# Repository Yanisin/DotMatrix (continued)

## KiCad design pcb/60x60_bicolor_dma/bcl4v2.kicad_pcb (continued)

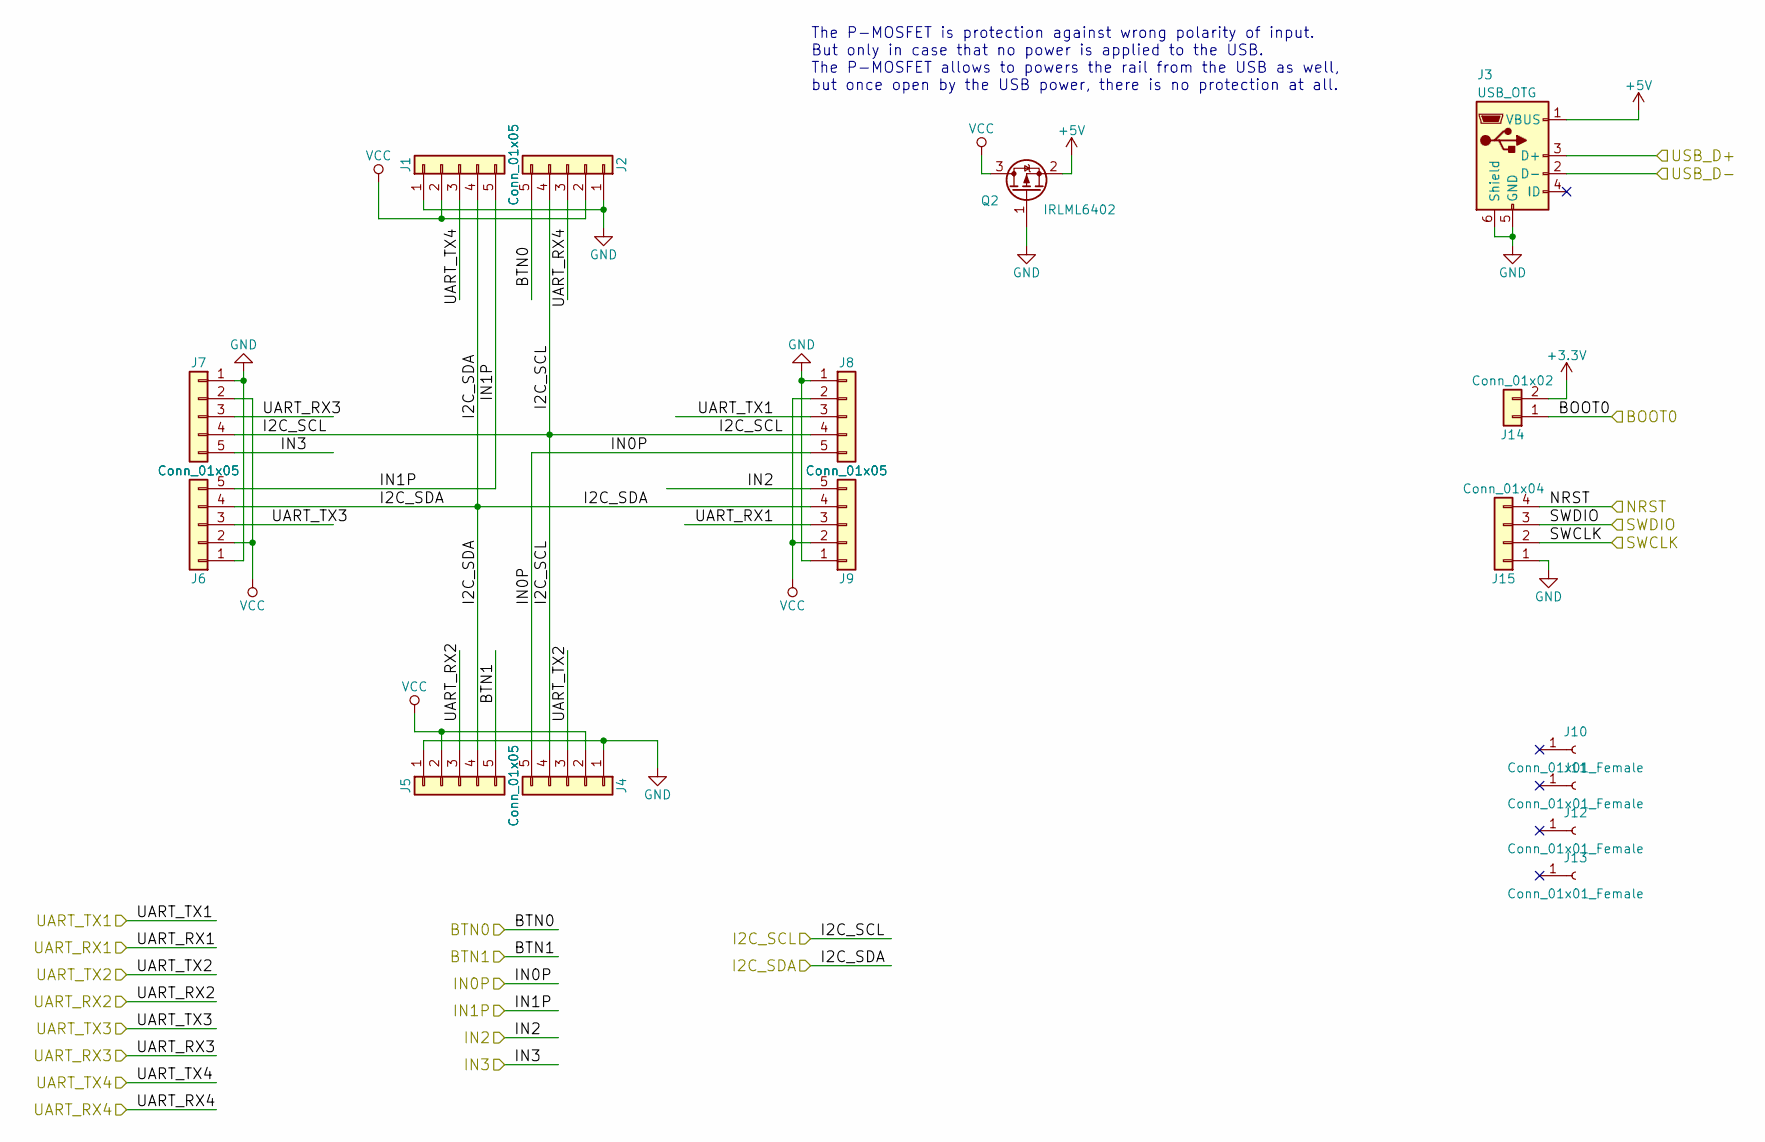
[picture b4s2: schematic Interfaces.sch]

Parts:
J1, J2, J4, J5, J6, J7, J8, J9: Conn_01x05; badger_Pin_Hdr_1x05_2.54mm_handsolder
J3: USB_OTG; USB_Micro-B
J10, J11, J12, J13: Conn_01x01_Female; badger_mount_M3
J14: Conn_01x02; badger_Pin_Hdr_1x02_2.54mm_angled_handsolder
J15: Conn_01x04; badger_Pin_Hdr_1x04_2.54mm_angled_handsolder
Q2: IRLML6402; badger_SOT-23_handsolder

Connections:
+3V3: J14.2; also elsewhere on the board
+5V: J3.1 (VBUS), Q2.2 (S); also elsewhere on the board
/BOOT0: J14.1; also elsewhere on the board
/BTN0: J2.5; also elsewhere on the board
/BTN1: J5.5; also elsewhere on the board
/I2C_SCL: J2.4, J4.4, J7.4, J8.4; also elsewhere on the board
/I2C_SDA: J1.4, J5.4, J6.4, J9.4; also elsewhere on the board
/IN0P: J4.5, J8.5; also elsewhere on the board
/IN1P: J1.5, J6.5; also elsewhere on the board
/IN2: J9.5; also elsewhere on the board
/IN3: J7.5; also elsewhere on the board
/NRST: J15.4; also elsewhere on the board
/SWCLK: J15.2; also elsewhere on the board
/SWDIO: J15.3; also elsewhere on the board
/UART_RX1: J9.3; also elsewhere on the board
/UART_RX2: J5.3; also elsewhere on the board
/UART_RX3: J7.3; also elsewhere on the board
/UART_RX4: J2.3; also elsewhere on the board
/UART_TX1: J8.3; also elsewhere on the board
/UART_TX2: J4.3; also elsewhere on the board
/UART_TX3: J6.3; also elsewhere on the board
/UART_TX4: J1.3; also elsewhere on the board
/USB_D+: J3.3 (D+); also elsewhere on the board
/USB_D-: J3.2 (D-); also elsewhere on the board
GND: J1.1, J2.1, J3.5 (GND), J3.6 (Shield), J4.1, J5.1, J6.1, J7.1, J8.1, J9.1, J15.1, Q2.1 (G); also elsewhere on the board
VCC: J1.2, J2.2, J4.2, J5.2, J6.2, J7.2, J8.2, J9.2, Q2.3 (D)

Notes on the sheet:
The P-MOSFET is protection against wrong polarity of input. But only in case that no power is applied to the USB. The P-MOSFET allows to powers the rail from the USB as well, but once open by the USB power, there is no protection at all.

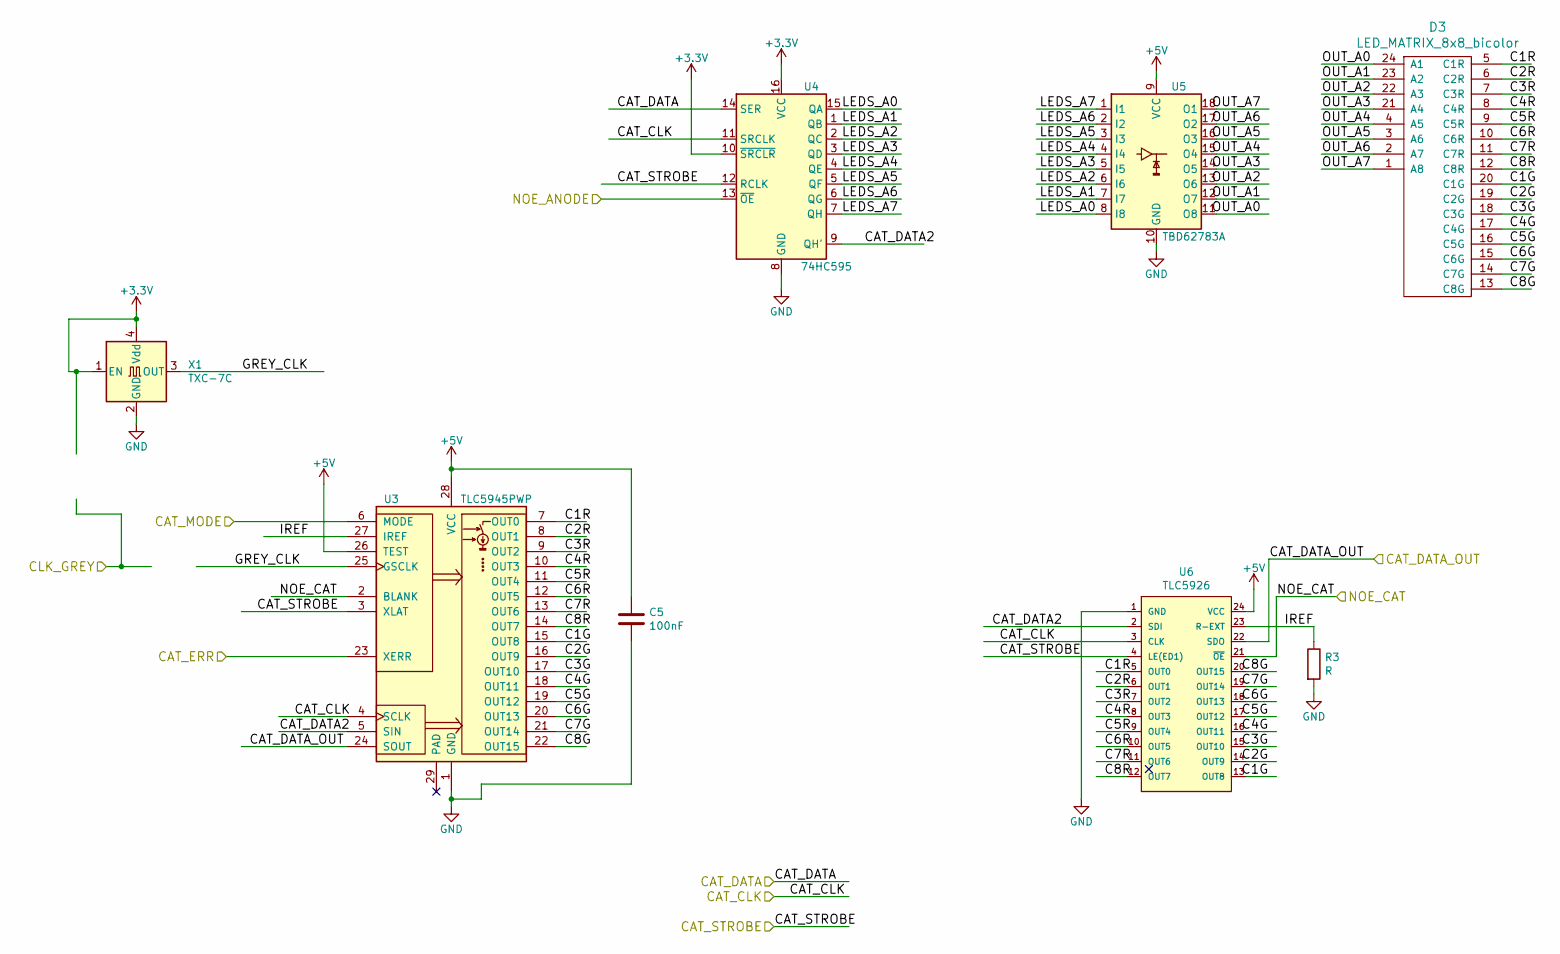
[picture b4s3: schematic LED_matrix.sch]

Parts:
C5: 100nF; C_0805_HandSoldering
D3: LED_MATRIX_8x8_bicolor; badger_LED_MATRIX_8x8_60.2mmx60.2mm_bicolor
R3: R; R_0805_HandSoldering
U3: TLC5945PWP; HTSSOP-28_4.4x9.7mm_Pitch0.65mm_wo_thermal_pad
U4: 74HC595; SO-16-N
U5: TBD62783A; SOIC-18W_7.5x11.6mm_Pitch1.27mm
U6: TLC5926; SOIC-24W_7.5x15.4mm_Pitch1.27mm
X1: TXC-7C; Oscillator_SMD_EuroQuartz_XO53-4pin_5.0x3.2mm_HandSoldering

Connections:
+3V3: U4.10 (~SRCLR), U4.16 (VCC), X1.1 (EN), X1.4 (Vdd); also elsewhere on the board
+5V: C5.1, U3.26 (TEST), U3.28 (VCC), U5.9 (VCC), U6.24 (VCC); also elsewhere on the board
/CAT_CLK: U3.4 (SCLK), U4.11 (SRCLK), U6.3 (CLK); also elsewhere on the board
/CAT_DATA: U4.14 (SER); also elsewhere on the board
/CAT_DOUT: U3.24 (SOUT), U6.22 (SDO); also elsewhere on the board
/CAT_ERR: U3.23 (XERR); also elsewhere on the board
/CAT_MODE: U3.6 (MODE); also elsewhere on the board
/CAT_STROBE: U3.3 (XLAT), U4.12 (RCLK), U6.4 (LE(ED1)); also elsewhere on the board
/LED_matrix/C1G: D3.20 (C1G), U3.15 (OUT8), U6.13 (OUT8)
/LED_matrix/C1R: D3.5 (C1R), U3.7 (OUT0), U6.5 (OUT0)
/LED_matrix/C2G: D3.19 (C2G), U3.16 (OUT9), U6.14 (OUT9)
/LED_matrix/C2R: D3.6 (C2R), U3.8 (OUT1), U6.6 (OUT1)
/LED_matrix/C3G: D3.18 (C3G), U3.17 (OUT10), U6.15 (OUT10)
/LED_matrix/C3R: D3.7 (C3R), U3.9 (OUT2), U6.7 (OUT2)
/LED_matrix/C4G: D3.17 (C4G), U3.18 (OUT11), U6.16 (OUT11)
/LED_matrix/C4R: D3.8 (C4R), U3.10 (OUT3), U6.8 (OUT3)
/LED_matrix/C5G: D3.16 (C5G), U3.19 (OUT12), U6.17 (OUT12)
/LED_matrix/C5R: D3.9 (C5R), U3.11 (OUT4), U6.9 (OUT4)
/LED_matrix/C6G: D3.15 (C6G), U3.20 (OUT13), U6.18 (OUT13)
/LED_matrix/C6R: D3.10 (C6R), U3.12 (OUT5), U6.10 (OUT5)
/LED_matrix/C7G: D3.14 (C7G), U3.21 (OUT14), U6.19 (OUT14)
/LED_matrix/C7R: D3.11 (C7R), U3.13 (OUT6), U6.11 (OUT6)
/LED_matrix/C8G: D3.13 (C8G), U3.22 (OUT15), U6.20 (OUT15)
/LED_matrix/C8R: D3.12 (C8R), U3.14 (OUT7), U6.12 (OUT7)
/LED_matrix/CAT_DATA2: U3.5 (SIN), U4.9 (QH'), U6.2 (SDI)
/LED_matrix/GREY_CLK: U3.25 (GSCLK), X1.3 (OUT)
/LED_matrix/IREF: R3.1, U3.27 (IREF), U6.23 (R-EXT)
/LED_matrix/LEDS_A0: U4.15 (QA), U5.8 (I8)
/LED_matrix/LEDS_A1: U4.1 (QB), U5.7 (I7)
/LED_matrix/LEDS_A2: U4.2 (QC), U5.6 (I6)
/LED_matrix/LEDS_A3: U4.3 (QD), U5.5 (I5)
/LED_matrix/LEDS_A4: U4.4 (QE), U5.4 (I4)
/LED_matrix/LEDS_A5: U4.5 (QF), U5.3 (I3)
/LED_matrix/LEDS_A6: U4.6 (QG), U5.2 (I2)
/LED_matrix/LEDS_A7: U4.7 (QH), U5.1 (I1)
/LED_matrix/OUT_A0: D3.24 (A1), U5.11 (O8)
/LED_matrix/OUT_A1: D3.23 (A2), U5.12 (O7)
/LED_matrix/OUT_A2: D3.22 (A3), U5.13 (O6)
/LED_matrix/OUT_A3: D3.21 (A4), U5.14 (O5)
/LED_matrix/OUT_A4: D3.4 (A5), U5.15 (O4)
/LED_matrix/OUT_A5: D3.3 (A6), U5.16 (O3)
/LED_matrix/OUT_A6: D3.2 (A7), U5.17 (O2)
/LED_matrix/OUT_A7: D3.1 (A8), U5.18 (O1)
/NOE_ANODE: U4.13 (~OE); also elsewhere on the board
/NOE_CAT: U3.2 (BLANK), U6.21 (~OE); also elsewhere on the board
GND: C5.2, R3.2, U3.1 (GND), U4.8 (GND), U5.10 (GND), U6.1 (GND), X1.2 (GND); also elsewhere on the board

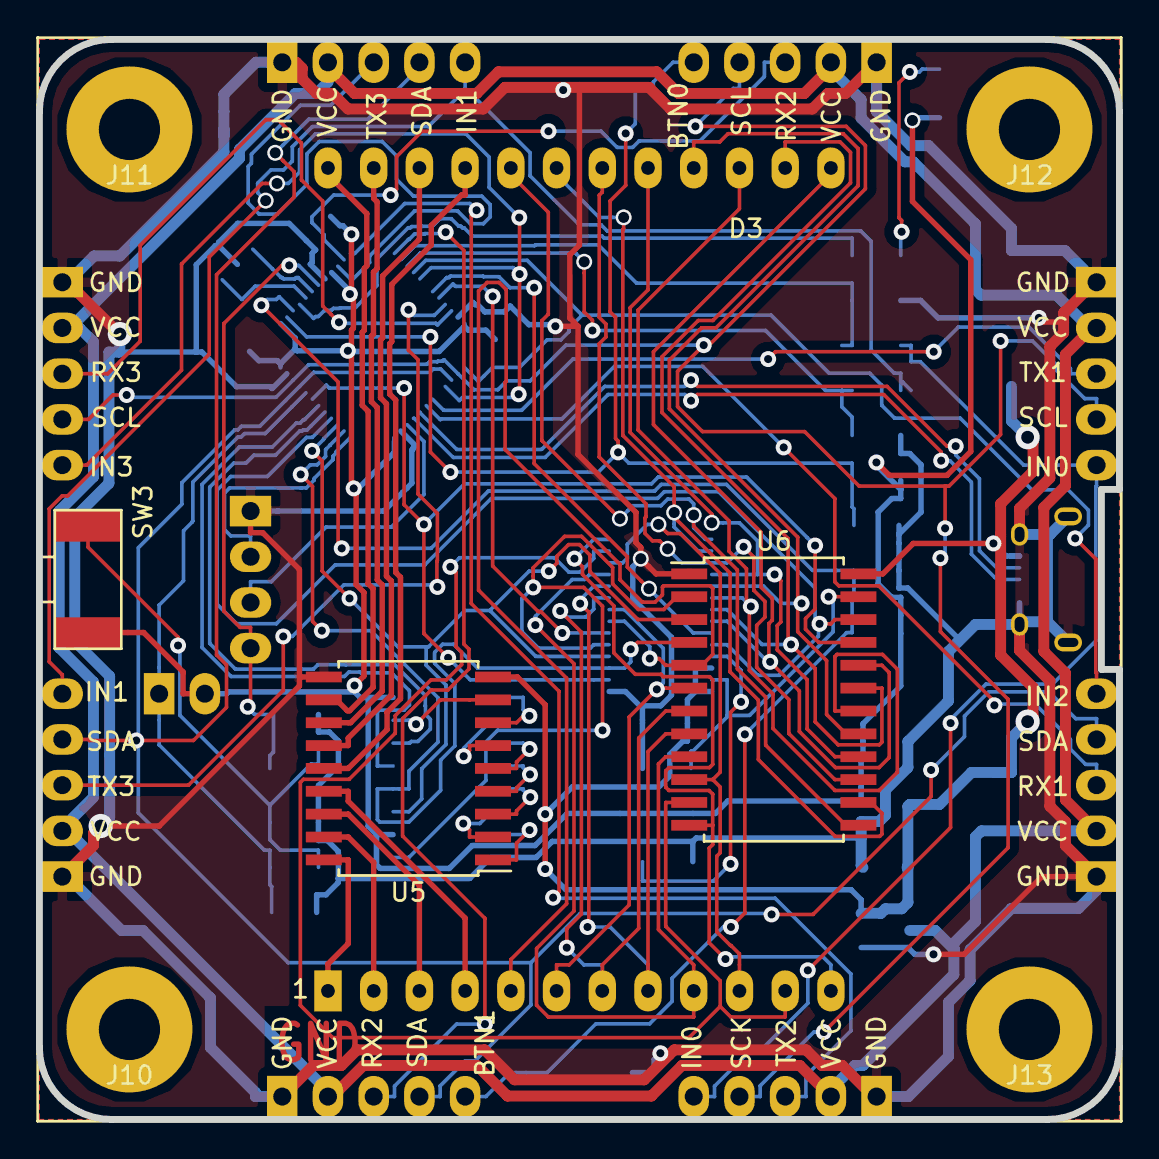
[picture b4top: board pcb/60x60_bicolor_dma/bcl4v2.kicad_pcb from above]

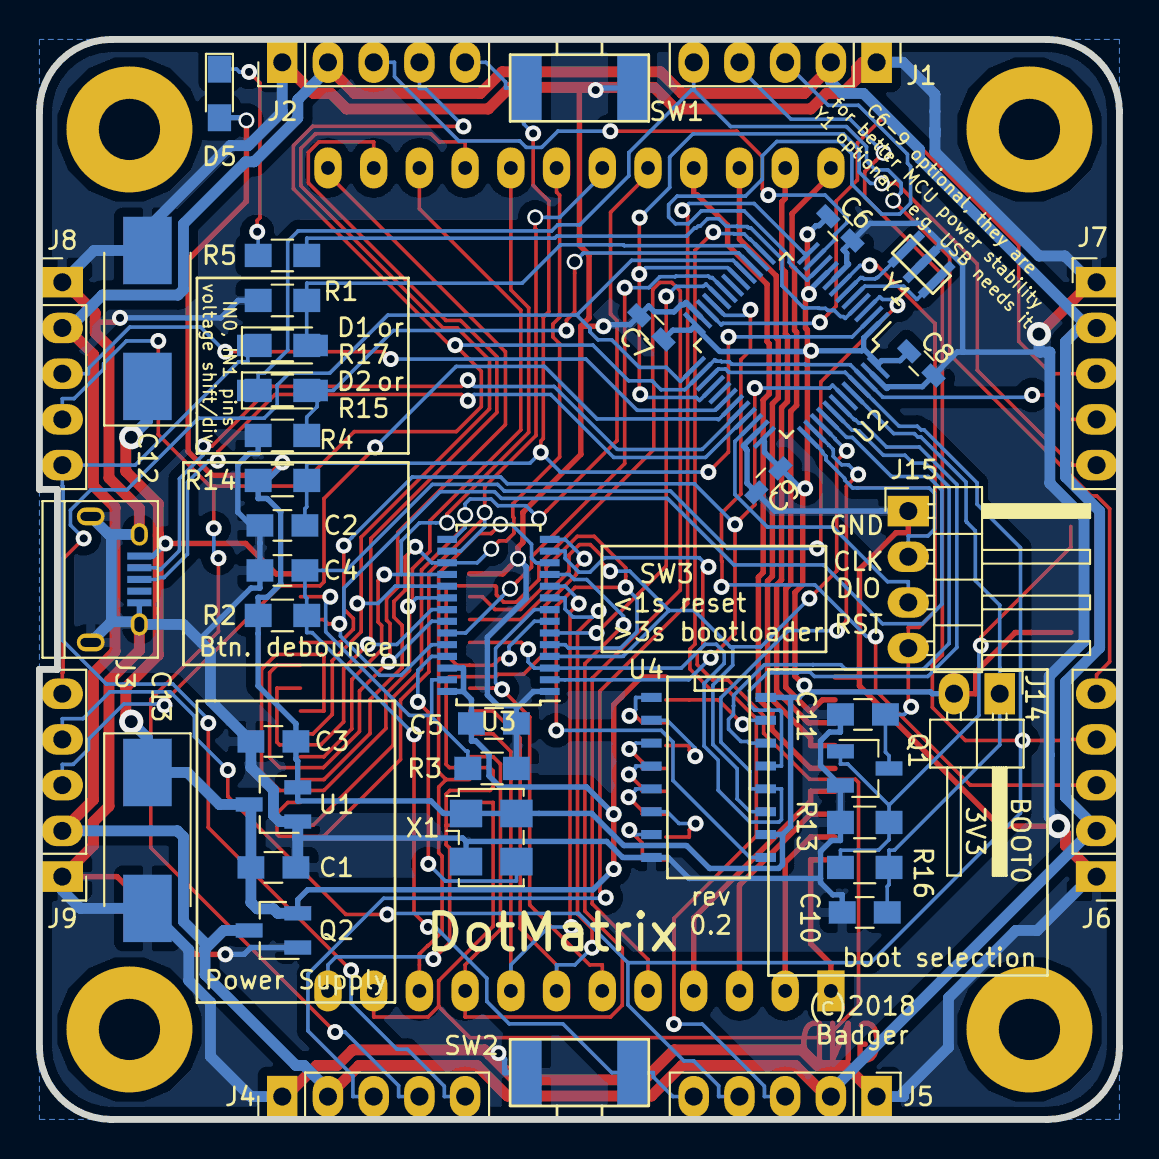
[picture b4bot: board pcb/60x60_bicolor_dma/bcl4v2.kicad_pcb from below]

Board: 2 copper layers, 60.0 x 60.0 mm, 55 parts (47 on the bottom side), 76 nets.

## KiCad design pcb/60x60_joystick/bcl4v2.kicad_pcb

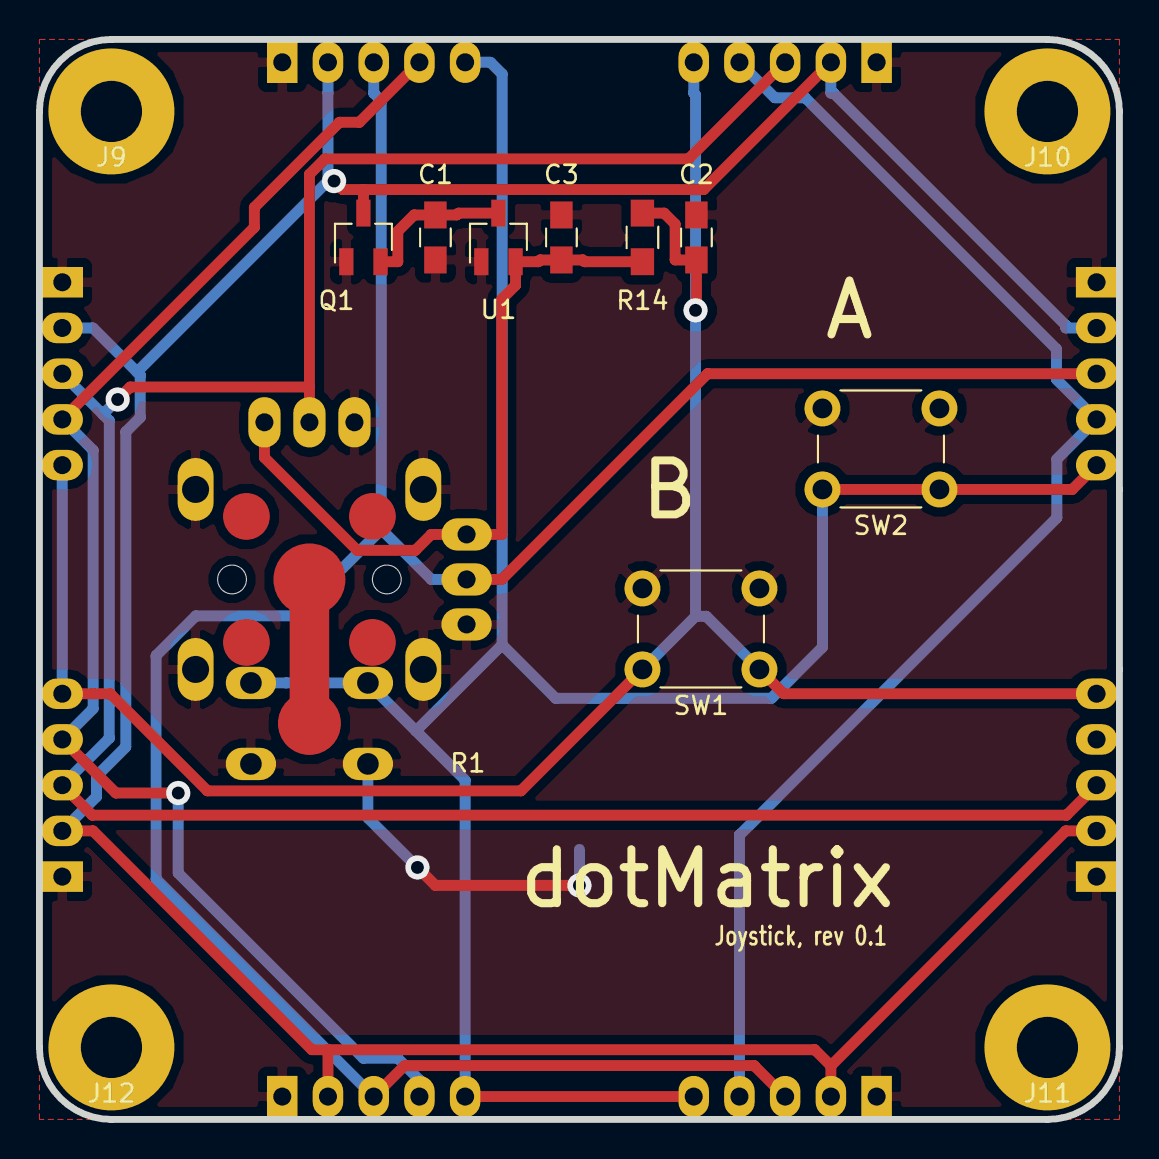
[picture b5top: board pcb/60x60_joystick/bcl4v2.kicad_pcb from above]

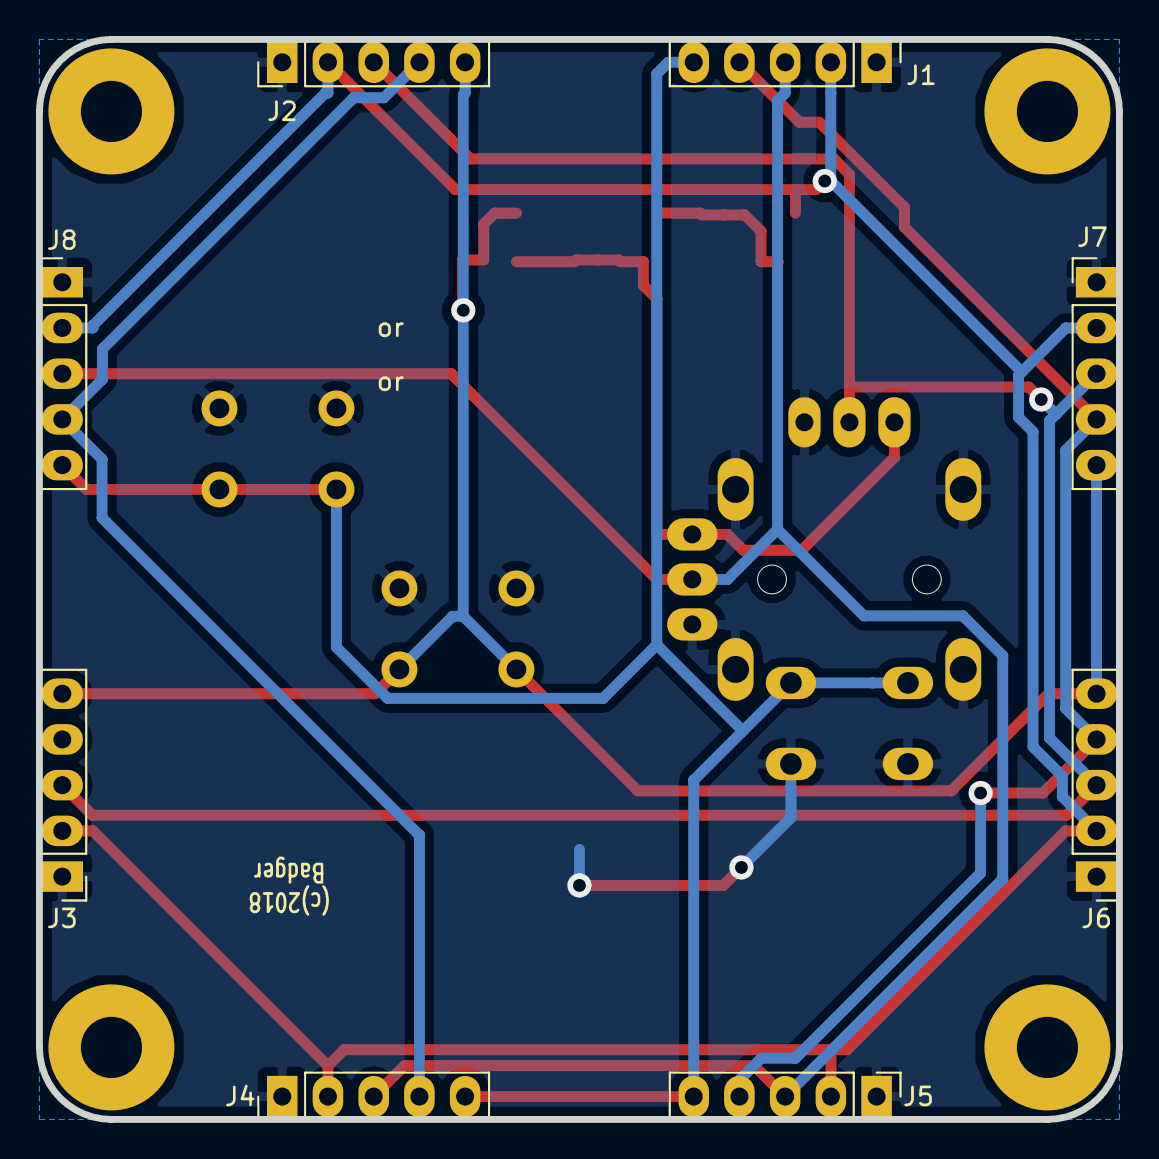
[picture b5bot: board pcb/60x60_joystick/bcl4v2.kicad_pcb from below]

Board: 2 copper layers, 60.0 x 60.0 mm, 21 parts (8 on the bottom side), 10 nets.

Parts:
C1, C3: 4u7; C_0805_HandSoldering
C2: 100n; C_0805_HandSoldering
J1, J2, J3, J4, J5, J6, J7, J8: Conn_01x05; badger_Pin_Hdr_1x05_2.54mm_handsolder
J9, J10, J11, J12: Conn_01x01_Female; badger_mount_M3
Q1: IRLML6402; badger_SOT-23_handsolder
R1: RKJXV1224_Joystick; badger_RKJXV1224 Joystick
R14: 220k; R_0805_HandSoldering
SW1, SW2: SW_Push; SW_PUSH_6mm_h5mm
U1: DS9166A-23; badger_SOT-23_handsolder

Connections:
+3V3: C3.1, R1.1, R1.4, R14.1, U1.2
+5V: C1.1, Q1.2, U1.3
/AOUT0: J2.3, J3.3, J6.3, J7.3, R1.2
/AOUT1: J1.3, J4.3, J5.3, J8.3, R1.5
/BTN0: J1.5, J4.5, J5.5, J8.5, R1.7, R1.8, SW2.1
/BTN1: C2.2, J2.5, J3.5, J6.5, J7.5, R14.2, SW1.1
/I2C_SCL: J1.4, J5.4, J6.4, J7.4
/I2C_SDA: J2.4, J4.4, J8.4
GND: C1.2, C2.1, C3.2, J1.1, J2.1, J3.1, J4.1, J5.1, J6.1, J7.1, J8.1, Q1.1, R1.3, R1.6, R1.9, R1.10, R1.11, R1.12, R1.13, R1.14, SW1.2, SW2.2, U1.1
VCC: J1.2, J2.2, J3.2, J4.2, J5.2, J6.2, J7.2, J8.2, Q1.3

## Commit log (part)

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2018-10-25 - add first prototype version of PCB
2018-10-25 - add some demos sketches without much of cleaning
2018-10-25 - use the CERN OHL v1.2
2018-10-28 - add errata for HW revision 0.1
2018-10-28 - draft of 60x60mm version
2018-10-28 - brainstorming what can be connected to headers
2018-10-28 - make the headers better solderable
2018-10-29 - split schematics to more pages
2018-11-01 - add pins to the sheets, add reset/boot circuit
2018-11-03 - replaced protection LEDs with mosfet
2018-11-03 - pcb (hopefully) ready for first routing attempt
2018-11-03 - little bit more componnent shifting to ease soldering
2018-11-03 -add missing LCD component footprint
2018-11-03 - don't commit kicad backup files
2018-11-03 - fix some footprints to reduce ERC errors
2018-11-03 - no need for edge cut for USB here
2018-11-03 - just before importing routed pcb from freeroute
2018-11-03 - imported freeroute output
2018-11-03 - fix silkscreen
2018-11-03 - yet another silkscreen fine tuning
2018-11-12 - add note about mounting hole spacing
2018-11-13 Add LED matrix symbol/footprint
2018-11-13 Board update
    fully routed PCB
    indicator LED added
2018-11-14 Add STEP model for USB receptacle
    Source:
    https://www.digikey.com/product-detail/en/amphenol-fci/10118194-0001LF/609-4618-1-ND/2785382
2018-11-18 PCB updates for panelization
    - place USB receptacle and edge cut-out smack center of the right board edge
    - rounded cut-out (.4mm radius) to allow routing it out using a single
    0.8mm wide slot.
2018-11-19 - quick sketch of bicolor 60x60 pcb
2018-11-25 - add prg_usb target
2018-11-25 - don't commit results of build process
2018-11-25 - add missing header, more cleanup
2018-11-25 - don't commit bin files
2018-11-25 - make hw config selectable during compile time
2018-11-25 - switch to next hw revision
2018-11-27 PCB and schematics cleanup
    resize PCB to exactly 38x38mm, center the LED matrix
    add OSHW logo to silk screen, add copyright information
2018-11-28 prg: use the "program" macro to flash the target
    canonical method to flash a target is:
    "program ELF.elf verify reset exit"
    which takes care of everything. ELF file must be linked for the correct
    address in flash.
2018-11-28 Makefile: provide TOPDIR variable
    useful to address OPENCM3 relative to the project root.
2018-11-30 Add test points, small routing changes
    - add test points for SPI bus
    - add net classes for VCC and LED networks
    - small routing changes
2018-12-05 correct dependency for "prg" target
    oocd programming only needs the ELF file
    also, use the preset OOCD variable to start openocd
2018-12-07 Support for 38x38 v3 tile with DMA
    Lots of changes in this one
    - display scan-out with DMA
    - remove generic timer interrupts
    - PRNG with xorshift32
    - overall clean-up, removing lots of dead and ifdef'd code,
    formatting cleanup
2018-12-07 make life less boring
    - fix rule computation, cell death must be instant, but life may have
    shades of red
    - add a few heuristics to catch stagnant (boring) populations
2018-12-07 small pcb fixes
    move USB_VBUS via out from under the USB receptacle (ouch)
    it just makes handsoldering difficult because the shield of
    the receptacle sucks up superfluous tin and then shorts
    USB_VBUS to ground
2018-12-14 disp: add fast version of disp_set
    add disp_set_noupdate() which only sets the display buffer
    but doesn't update the DMA row buffer. Useful for bulk
    updates of the display that touch all rows multiple times.
    also add disp_update_rows() to update all DMA row buffers
    at once.
2018-12-14 usart: new method for USART assignment to edge
    USARTS are now internally enumerated from A to D and their
    base pointers are stored in an array indexed from 0 to 3.
    Assignment of edges to USARTS is through symbolic name
    USART_[A-D]. usart_init() needs to be called in order
    A to D to match ISR assignments of rx/tx buffers.
    Also some cleanups and removal of dead/commented code.
2018-12-21 Correct display orientation to make (0,0) top left
    hardware should be reflected in the software.
2018-12-21 refactor usart_buffered.c
    - move common isr code into single function
    - simplify ring buffer operations, make them easier to understand
2019-01-01 Add CDCACM USB function
    Serial line for debug and control
2019-01-01 Cleanup main()
    add cpu_relax() inline function to execute "wfi" in the main loop
    general cleanup
2019-01-01 Cleanup usart_buffered API, add usart_buf_clear()
2019-01-06 Add simple serial console over CDCACM
    add the following functions:
    - console_printf (warning, adds a lot of library code!)
    - console_putc
    - console_puts
    - console_getc
2019-01-06 life: switch trace output to the console layer
2019-01-06 life: fix life tick updates
    compute life tick through a multiplier and update the multiplier
    once every tick based on console input
2019-01-06 life: update interpretation of S23/B36 rule
    cells are born with 3 and 6 neighbors and also survive with 6 neighbors
    not sure if this is correct but the results seem to be OK.
2019-01-15 - copy led driving schematic, from 38x38_dma, change switches
2019-01-18 - just before autoroute
2019-02-12 - add 60x60_dma version
2019-02-18 PCB updates: 32kHz oscillator, separate VBAT supply
    also, longer pads for the row driver
2019-02-18 console: console_printf made configurable
    can be left out of the build to save flash space
2019-02-18 rtc: rtc initialization and time-set over cdcacm
2019-02-18 wordclock: simple wordclock app
    "FIVE TO NINE"
2019-02-18 make: add rtc and wordclock to compile
2019-02-19 introduce "applet" mini-framework
    Minimal framework for "applets" running from the main loop. A
    new "struct applet" keeps pointers to an "init" and a "worker" function.
    A "struct applet" instance can be registered with the framework by the
    macro "applet_add", which puts an instance pointer into a dedicated ELF
    section. Two functions applet_init_all() and applet_run_all() are then
    called from main() to run the init and worker functions. This removes
2019-02-19 wordclock: small corrections
    "A QUARTER" instead of "QUARTER"
    remove an "unused function" warning
    remove a debug print
2019-02-20 add udev hotplug rule
    to set the wordclock when connected
2019-03-24 - fix display connections, add testpoints
2019-03-26 - add LSE crystal (needs to fix routing and zones)
2019-03-31 - larger USB pads, larger switch cuts, silk fixes
2019-03-31 - panelize in design
2019-04-16 - partially filled BOM
2019-04-16 - add more details in BOM
2019-04-20 - rename the demo
2019-04-20 - add bitbang tests
2019-04-20 - merge in dma branch and lot of fixups - merge in dma branch - some renaming in the header file, to make it more consistent - workaround for wrong column order in rev 0.4, need to be reverted for ne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
2019-04-21 - add simple (useless for now) button example
2019-04-28 - add OSHV logo, move LED a bit
2019-04-28 -refill zones
2019-04-28 - drop the compress fabrication output
2019-04-28 - add display support and joints
2019-04-28 - add brief readme
2019-05-27 - add bards joint scad file
2019-05-27 -add cut for LED on rev 0.5
2019-05-27 Initial version of the simulator, can show the display and LED status.
2019-05-31 Restore the ability to run on a real device.
2019-06-02 Support uart and gpio in simulator.
    The UART was also reworked to support framing for some future
    applications.
2019-06-02 Fix the sim ticker.
2019-06-02 Topology detection works in simulator.
    Target not buildable.
2019-06-02 Fix the position transmission.
    The vectors were rotated the other way around.
2019-06-03 Make it actually work on a device.
2019-06-03 Add button support on real device.
2019-06-03 fix broken workers
2019-06-03 Hopefully, finally fix cdcacm.
2019-06-03 Re-organize makefiles.
    - Target and simulator binaries are built at once
    - Shared C definitions for sim and target
    - Separate build directories
    - Automatic dependencies from sim build
    - Hopefully less boilerplate
    - settings.mk file for user-specific stuff (not part of GIT).
2019-06-03 Get rid of warnings.
2019-06-03 Original code drop.
2019-06-03 Add basic Distributed DFU support.
    Currently it is not distributed, but it is DFU.
2019-06-04 Use correct header memory.h -> string.h
2019-06-05 Test ChibiOS in the full demo.
    The plan is to move the GameOfLife demo to ChibiOS and leave striped
    down teaching GameOfLife demo.
2019-06-05 Move GameOfLife demo to the full directory
    (the name was not valid anyway)
    It does not utilize ChibiOS in any way yet, except that it runs as a
    task.
2019-06-05 Working sim & device under ChibiOS.
    Still does not take advantage of the OS.
2019-06-08 Fix some usart problems on target and increase stack.
    _snprintf is a memory hog.
2019-06-08 Initializer rework & button support.
    We do not need the full worker infrastructure, we can fire of tasks or
    register virtual timers instead of polling.
2019-06-08 Make sure master = 0, makes better sense.
    Handle sigsegvs.
2019-06-08 - clense the schematics
2019-06-08 - allow setting path to the arm-none-eabi in settings.mk
2019-06-08 - update bitbang tests
2019-06-08 - disabled display
2019-06-08 - replace smile with disp driver test
2019-06-09 I2C support. Life and applet chooser ported to i2c.
2019-06-09 Change the mechanism for selecting gcc directory and/or prefix.
2019-06-09 - add assembly manual
2019-06-09 - improve readability of the manual
2019-06-09 Fix chooser applet timeout.
2019-06-09 Add automatic synchronization to USART.
2019-06-09 - enable pullups on the buttons
2019-06-09 Fix dfu page 0 not being flashed on slaves.
2019-06-09 Simplify & improve HW cleanup by doing peripheral reset.
2019-06-09 Integrate the display test.
2019-06-10 Add stack checker.
2019-06-10 Fix GameOfLife queing. Should also fix _ack in the future to prevent this mistake.
2019-06-10 Ressurrect @maw's Game of life.
2019-06-10 Port display test back to the simple GameOfLife.
2019-06-10 Harden DFU i2c.
    1) Make sure the slave times out if it receives no instructions.
    2) The master times out on sending the release packet if it can not be
    sent.
2019-06-10 Small i2c TX rewrite.
    Main problem was the reversed sense of binary semaphore (also fixed in
    buttons) and not enabled STOPIE.
2019-06-10 Disable bus stretching and enable pullups.
    Pullups on all should be OK for a large number of cells and improve signal quality.
    Clock stretching has great potential for locking up the bus.
2019-06-10 Remove the debug on reject and fix some OOB in i2c rx.
2019-06-10 Add i2c recovery features.
    There was also nasty bug with calling console_printf in ISR. And
    console_printf uses exuberant amount of stack.
2019-06-10 Fix warning.
2019-06-10 Use custom printf.
2019-06-11 Push the programming to the background.
    Remove extra file commited by mistake.
2019-06-11 Switch the wait_for_dfu script to polling.
    The wait for device phase can also be skipped.
2019-06-11 Fix some communication errors on larger setups.
    Bootloader had wrong even/odd i2c detection and similar problem was in
    the even/odd i2c based on topology in full demo (caused by the ABS
    function).
2019-06-11 Allocate the default message queues statically.
2019-06-11 Add CDCACM support.
    Maybe a shell is coming next?
2019-06-12 add Dockerfile with toolchain and updated readme
2019-06-12 Reorganize files (rename phase).
2019-06-12 Fixup paths after rename.
2019-06-12 Improve error messages when build mod is missing (but make build less generic).
2019-06-12 Reformat & verify the old demos with bootloader.
    Robert reported they were not working. Miniblink was indeed broken.
2019-06-12 Fix misleading file name.
2019-06-12 Scroller demo.
2019-06-14 - update schematics export, few words about hw
2019-06-14 - rewrite bootloader section of readme
2019-06-14 - add hello world applet
2019-06-14 Add scroller applet.
2019-06-14 Add 1d cellular automata.
2019-06-14 Document memory map.
2019-06-14 Remove worldclock - not relevant for the soldering workshop.
2019-06-14 Add full demo readme.
2019-06-14 Doxygen.
2019-07-08 -- pogo pin connector attempt
